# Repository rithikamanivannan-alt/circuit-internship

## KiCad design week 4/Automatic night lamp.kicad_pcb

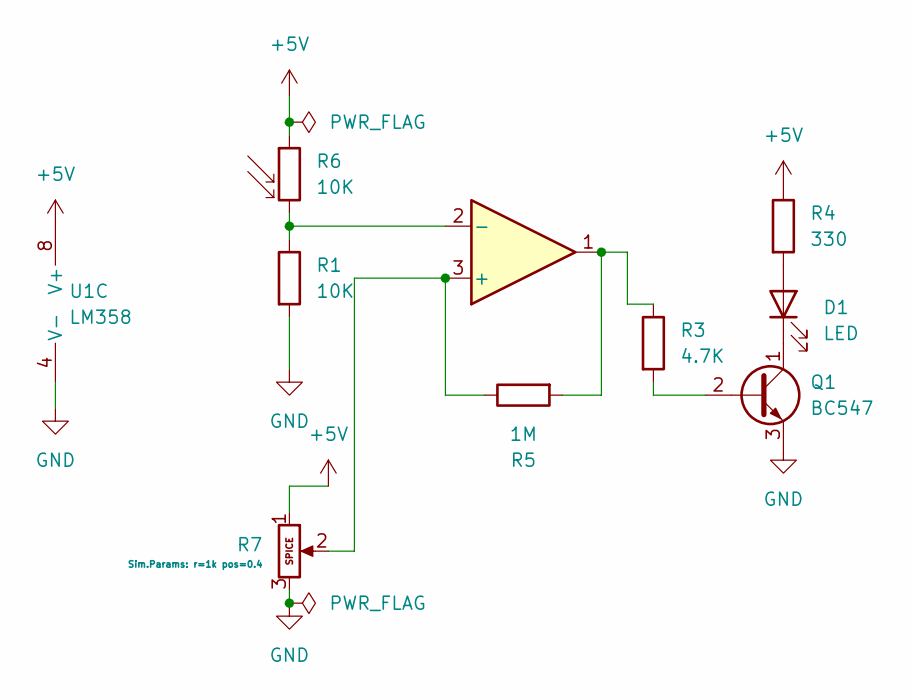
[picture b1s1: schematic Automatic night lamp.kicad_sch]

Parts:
D1: LED; LED_D5.0mm
Q1: BC547; TO-92_Inline
R1: 10K; R_Axial_DIN0204_L3.6mm_D1.6mm_P7.62mm_Horizontal
R3: 4.7K; R_Axial_DIN0204_L3.6mm_D1.6mm_P7.62mm_Horizontal
R4: 330; R_Axial_DIN0204_L3.6mm_D1.6mm_P7.62mm_Horizontal
R5: 1M; R_Axial_DIN0204_L3.6mm_D1.6mm_P7.62mm_Horizontal
R6: 10K; R_LDR_5.1x4.3mm_P3.4mm_Vertical
R7: Potentiometer; Potentiometer_Alps_RK09K_Single_Vertical
U1: LM358; DIP-8_W7.62mm

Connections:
+5V: R4.1, R6.1, R7.1, U1.8 (V+)
GND: Q1.3 (E), R1.2, R7.3, U1.4 (V-)
unnamed: D1.2 (A), R4.2
unnamed: D1.1 (K), Q1.1 (C)
unnamed: Q1.2 (B), R3.2
unnamed: R3.1, R5.2, U1.1
unnamed: R5.1, R7.2, U1.3 (+)
unnamed: R1.1, R6.2, U1.2 (-)

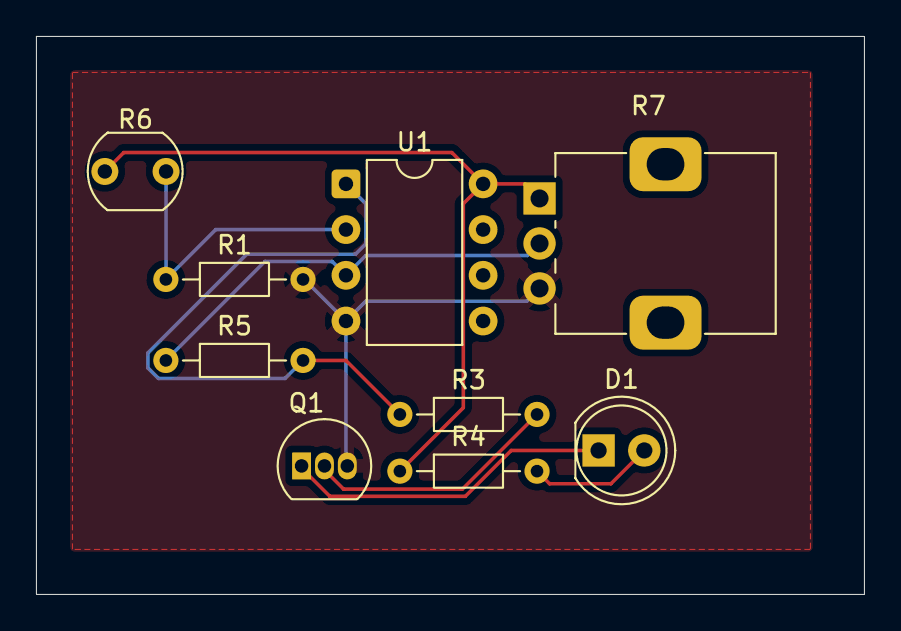
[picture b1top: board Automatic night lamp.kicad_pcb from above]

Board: 2 copper layers, 46.0 x 31.0 mm, 9 parts (0 on the bottom side), 8 nets.

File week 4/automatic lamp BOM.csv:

"Reference","Qty","Value","DNP","Exclude from BOM","Exclude from Board","Footprint","Datasheet"
"D1","1","LED","","","","LED_THT:LED_D5.0mm",""
"Q1","1","BC547","","","","Package_TO_SOT_THT:TO-92_Inline","https://www.onsemi.com/pub/Collateral/BC550-D.pdf"
"R1","1","10K","","","","Resistor_THT:R_Axial_DIN0204_L3.6mm_D1.6mm_P7.62mm_Horizontal",""
"R3","1","4.7K","","","","Resistor_THT:R_Axial_DIN0204_L3.6mm_D1.6mm_P7.62mm_Horizontal",""
"R4","1","330","","","","Resistor_THT:R_Axial_DIN0204_L3.6mm_D1.6mm_P7.62mm_Horizontal",""
"R5","1","1M","","","","Resistor_THT:R_Axial_DIN0204_L3.6mm_D1.6mm_P7.62mm_Horizontal",""
"R6","1","10K","","","","OptoDevice:R_LDR_5.1x4.3mm_P3.4mm_Vertical",""
"R7","1","Potentiometer","","","","Potentiometer_THT:Potentiometer_Alps_RK09K_Single_Vertical",""
"U1","1","LM358","","","","Package_DIP:DIP-8_W7.62mm","http://www.ti.com/lit/ds/symlink/lm2904-n.pdf"

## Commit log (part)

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2026-06-11 intern circuits
2026-06-18 week 2
2026-06-25 week 3
